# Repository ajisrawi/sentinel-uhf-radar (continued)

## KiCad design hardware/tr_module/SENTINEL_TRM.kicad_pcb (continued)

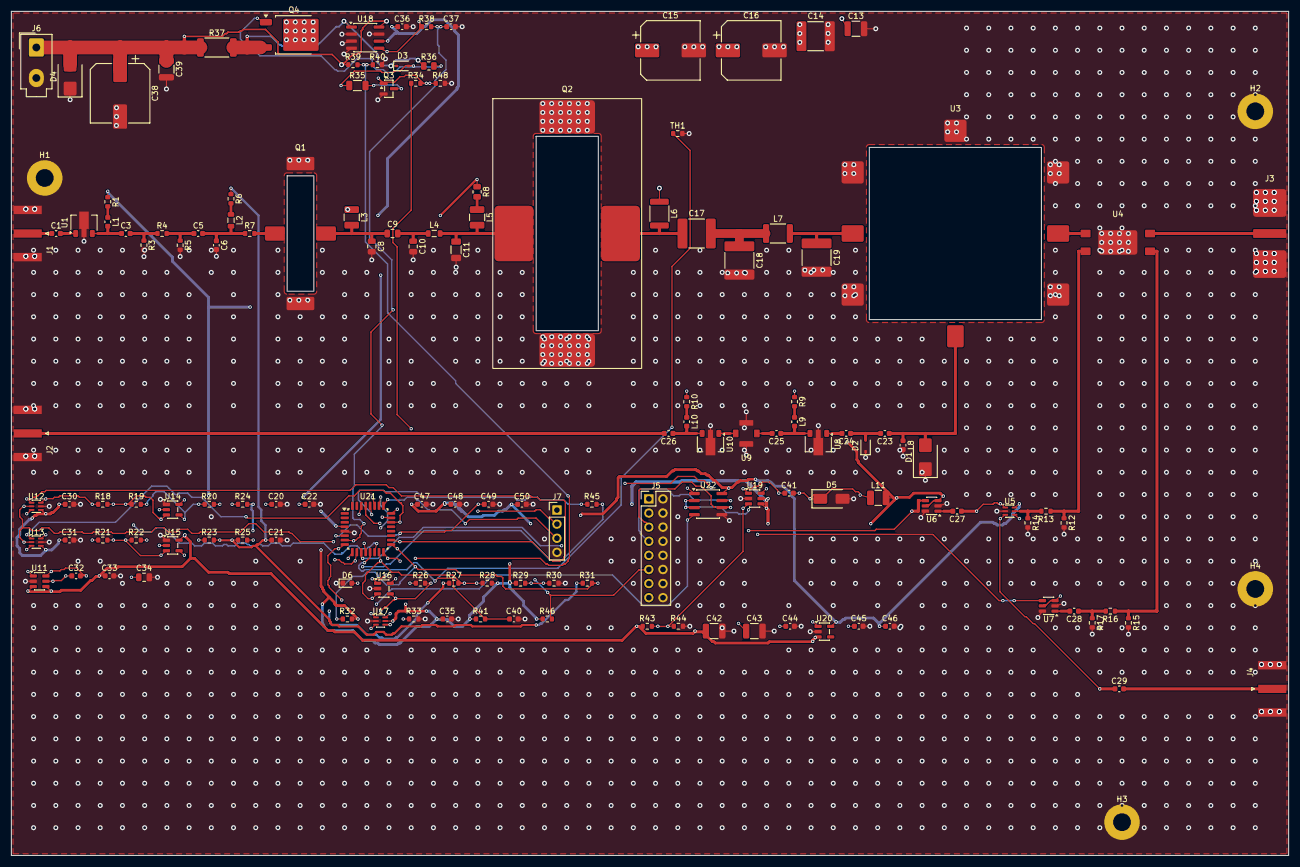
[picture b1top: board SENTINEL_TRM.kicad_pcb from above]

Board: 4 copper layers, 230.0 x 152.0 mm, 144 parts (0 on the bottom side), 90 nets.

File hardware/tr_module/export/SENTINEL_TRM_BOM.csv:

"Item","References","Qty","Value","Footprint","Description","MPN / part class"
"1","C1,C3,C23-C29","9","100p","Capacitor_SMD:C_0603_1608Metric","DC block, C0G",""
"2","C5","1","33p","Capacitor_SMD:C_0603_1608Metric","Driver input DC block",""
"3","C6","1","8.2p","Capacitor_SMD:C_0603_1608Metric","Driver input match",""
"4","C8","1","1.5p","Capacitor_SMD:C_0805_2012Metric","Driver output match",""
"5","C9","1","47p","Capacitor_SMD:C_0805_2012Metric","Interstage DC block",""
"6","C10","1","10p","Capacitor_SMD:C_0805_2012Metric","Interstage match",""
"7","C11","1","22p","Capacitor_SMD:C_1206_3216Metric","PA input match",""
"8","C13","1","1n 100V","Capacitor_SMD:C_1210_3225Metric","",""
"9","C14","1","10u 100V","Capacitor_SMD:C_2220_5750Metric","",""
"10","C15,C16","2","330u 63V","Capacitor_SMD:CP_Elec_10x10.5","Polymer, pulse reservoir",""
"11","C17","1","100p","Capacitor_SMD:C_2220_5750Metric","Output DC block, 500 V, high-Q",""
"12","C18","1","6.8p","Capacitor_SMD:C_2220_5750Metric","Output match, 500 V",""
"13","C19","1","3.3p","Capacitor_SMD:C_2220_5750Metric","Output match, 500 V",""
"14","C20,C21,C30,C31,C35,C36,C40,C41,C44,C47,C49,C50","12","100n","Capacitor_SMD:C_0603_1608Metric","",""
"15","C22,C32,C33,C45,C46","5","1u","Capacitor_SMD:C_0603_1608Metric","",""
"16","C34","1","4.7u","Capacitor_SMD:C_0805_2012Metric","",""
"17","C37","1","10n","Capacitor_SMD:C_0603_1608Metric","",""
"18","C38","1","100u 100V","Capacitor_SMD:CP_Elec_10x10.5","Bus bulk",""
"19","C39","1","1u 100V","Capacitor_SMD:C_1210_3225Metric","",""
"20","C42","1","22u","Capacitor_SMD:C_1210_3225Metric","",""
"21","C43","1","10u 50V","Capacitor_SMD:C_1210_3225Metric","",""
"22","C48","1","4.7u","Capacitor_SMD:C_0603_1608Metric","",""
"23","D1","1","PIN","Diode_SMD:D_SMB","Coarse PIN limiter diode, 100 W pk",""
"24","D2","1","Schottky","Diode_SMD:D_SOD-323","Fine limiter",""
"25","D3","1","12V","Diode_SMD:D_SOD-323","P-FET Vgs clamp",""
"26","D4","1","SMBJ58A","Diode_SMD:D_SMB","Bus transient clamp",""
"27","D5","1","SS16","Diode_SMD:D_SMA","",""
"28","D6","1","GRN","LED_SMD:LED_0603_1608Metric","Status LED",""
"29","H1-H4","4","M3","MountingHole:MountingHole_3.2mm_M3_Pad","Cold-plate bond, M3",""
"30","J1","1","TX_IN","Connector_Coaxial:SMA_Amphenol_132289_EdgeMount","SMA edge launch, RF drive from RFSoC DAC (0 dBm)",""
"31","J2","1","RX_OUT","Connector_Coaxial:SMA_Amphenol_132289_EdgeMount","SMA edge launch to RFSoC ADC",""
"32","J3","1","ANT","SENTINEL:N_EdgeLaunch","N-type edge launch to crossed-dipole hybrid",""
"33","J4","1","CAL","Connector_Coaxial:SMA_Amphenol_132289_EdgeMount","SMA to array calibration network (mutual-coupling cal)",""
"34","J5","1","BACKPLANE","Connector_PinHeader_2.54mm:PinHeader_2x08_P2.54mm_Vertical","Tile backplane: aux power, RS-485, TX_EN gate, fault; even pins ground",""
"35","J6","1","50V IN","Connector_Molex:Molex_Mini-Fit_Jr_5566-02A_2x01_P4.20mm_Vertical","Mini-Fit Jr, 50 V drain bus from subarray supply",""
"36","J7","1","SWD","Connector_PinHeader_2.54mm:PinHeader_1x04_P2.54mm_Vertical","",""
"37","L1,L9,L10","3","390n","Inductor_SMD:L_0603_1608Metric","RF choke",""
"38","L2","1","220n","Inductor_SMD:L_0805_2012Metric","Gate feed",""
"39","L3","1","120n","Inductor_SMD:L_1210_3225Metric","Driver drain feed",""
"40","L4","1","18n","Inductor_SMD:L_0805_2012Metric","Interstage match",""
"41","L5","1","56n","Inductor_SMD:L_1210_3225Metric","PA gate feed",""
"42","L6","1","47n","Inductor_SMD:L_1812_4532Metric","PA drain feed, 10 A peak",""
"43","L7","1","8n","Inductor_SMD:L_1812_4532Metric","Output match, air core",""
"44","L8","1","100n","Inductor_SMD:L_0603_1608Metric","Limiter DC return",""
"45","L11","1","22u","Inductor_SMD:L_1210_3225Metric","",""
"46","Q1","1","GaN 10W","SENTINEL:GaN_Flange_440166","Driver GaN HEMT 10 W, 50 V, 440166 flange","CG2H40010F class"
"47","Q2","1","GaN 300W","SENTINEL:GaN_Flange_780","Final GaN HEMT 300 W pulsed, 50 V, NI-780 flange","UHF radar GaN, 300 W class"
"48","Q3","1","2N7002","Package_TO_SOT_SMD:SOT-23","Level shifter",""
"49","Q4","1","SUD50P10","Package_TO_SOT_SMD:TO-252-2","High-side drain switch, 100 V P-FET",""
"50","R1,R10","2","33","Resistor_SMD:R_0603_1608Metric","",""
"51","R3,R5","2","292","Resistor_SMD:R_0603_1608Metric","3 dB pi pad",""
"52","R4","1","17.6","Resistor_SMD:R_0603_1608Metric","3 dB pi pad",""
"53","R6","1","22","Resistor_SMD:R_0603_1608Metric","",""
"54","R7","1","4.7","Resistor_SMD:R_0603_1608Metric","Gate stability resistor",""
"55","R8","1","10","Resistor_SMD:R_0805_2012Metric","",""
"56","R9","1","47","Resistor_SMD:R_0603_1608Metric","",""
"57","R12,R14,R15,R17","4","96","Resistor_SMD:R_0603_1608Metric","",""
"58","R13,R16","2","71","Resistor_SMD:R_0603_1608Metric","10 dB pi pad",""
"59","R18,R21,R26,R33,R40,R41,R44,R46","8","10k","Resistor_SMD:R_0603_1608Metric","TX_EN defaults low",""
"60","R19,R22","2","12.4k","Resistor_SMD:R_0603_1608Metric","",""
"61","R20,R23","2","10","Resistor_SMD:R_0603_1608Metric","",""
"62","R24,R25,R27,R28,R31,R32,R48","7","100k","Resistor_SMD:R_0603_1608Metric","Fail-safe pinch-off",""
"63","R29","1","82k","Resistor_SMD:R_0603_1608Metric","",""
"64","R30","1","20k","Resistor_SMD:R_0603_1608Metric","",""
"65","R34","1","100","Resistor_SMD:R_0603_1608Metric","",""
"66","R35","1","10k","Resistor_SMD:R_1206_3216Metric","",""
"67","R36","1","4.7k","Resistor_SMD:R_0805_2012Metric","",""
"68","R37","1","5m","Resistor_SMD:R_2512_6332Metric","Drain current shunt, Kelvin",""
"69","R38,R45","2","1k","Resistor_SMD:R_0603_1608Metric","",""
"70","R39","1","180k","Resistor_SMD:R_0603_1608Metric","",""
"71","R43","1","56.2k","Resistor_SMD:R_0603_1608Metric","",""
"72","TH1","1","10k NTC","Resistor_SMD:R_0603_1608Metric","On PA flange",""
"73","U1","1","GB 20dB","Package_TO_SOT_SMD:SOT-89-3","Driver gain block, G 20 dB, P1dB +21 dBm","PHA-13LN+ class"
"74","U3","1","CIRC 400W","SENTINEL:Circulator_DropIn_32mm","Drop-in circulator 420-450 MHz, 400 W pk, 20 dB isolation",""
"75","U4","1","-30dB","SENTINEL:DirCoupler_SMD_12x6","Directional coupler 30 dB, 500 W",""
"76","U5","1","SPDT","Package_TO_SOT_SMD:SOT-363_SC-70-6","RF switch: detector or calibration port",""
"77","U6","1","DET FWD","Package_TO_SOT_SMD:SOT-23-6","Forward power detector",""
"78","U7","1","DET REV","Package_TO_SOT_SMD:SOT-23-6","Reflected power detector (VSWR trip)",""
"79","U8","1","LNA","Package_TO_SOT_SMD:SOT-89-3","LNA NF 0.5 dB, G 18 dB at 435 MHz",""
"80","U9","1","BPF 420-450","SENTINEL:BPF_SMD_5x5","SAW BPF 435 MHz, 30 MHz BW, IL 2 dB",""
"81","U10","1","GB 20dB","Package_TO_SOT_SMD:SOT-89-3","Receive gain block, G 20 dB",""
"82","U11","1","LM2776","Package_TO_SOT_SMD:SOT-23-6","-5 V for GaN gate bias",""
"83","U12,U13","2","DAC7311","Package_TO_SOT_SMD:SOT-363_SC-70-6","12-bit DAC, DRV gate setpoint,12-bit DAC, PA gate setpoint",""
"84","U14,U15","2","LM321","Package_TO_SOT_SMD:SOT-23-5","Inverting gate driver, +5/-5 V",""
"85","U16","1","LMV331","Package_TO_SOT_SMD:SOT-23-5","BIAS_OK high only when VG_PA < -2.0 V",""
"86","U17","1","74LVC1G11","Package_TO_SOT_SMD:SOT-363_SC-70-6","Drain on = TX_EN AND BIAS_OK AND MCU enable",""
"87","U18","1","INA240A1","Package_SO:SOIC-8_3.9x4.9mm_P1.27mm","Drain current sense, 20 V/V",""
"88","U19","1","LMR16006","Package_TO_SOT_SMD:SOT-23-6","12 V to 5 V buck, 0.6 A",""
"89","U20","1","AP2112K-3.3","Package_TO_SOT_SMD:SOT-23-5","",""
"90","U21","1","STM32G031K8T6","Package_QFP:LQFP-32_7x7mm_P0.8mm","Module controller: bias, protection, telemetry",""
"91","U22","1","THVD1450","Package_SO:SOIC-8_3.9x4.9mm_P1.27mm","RS-485 to tile controller",""

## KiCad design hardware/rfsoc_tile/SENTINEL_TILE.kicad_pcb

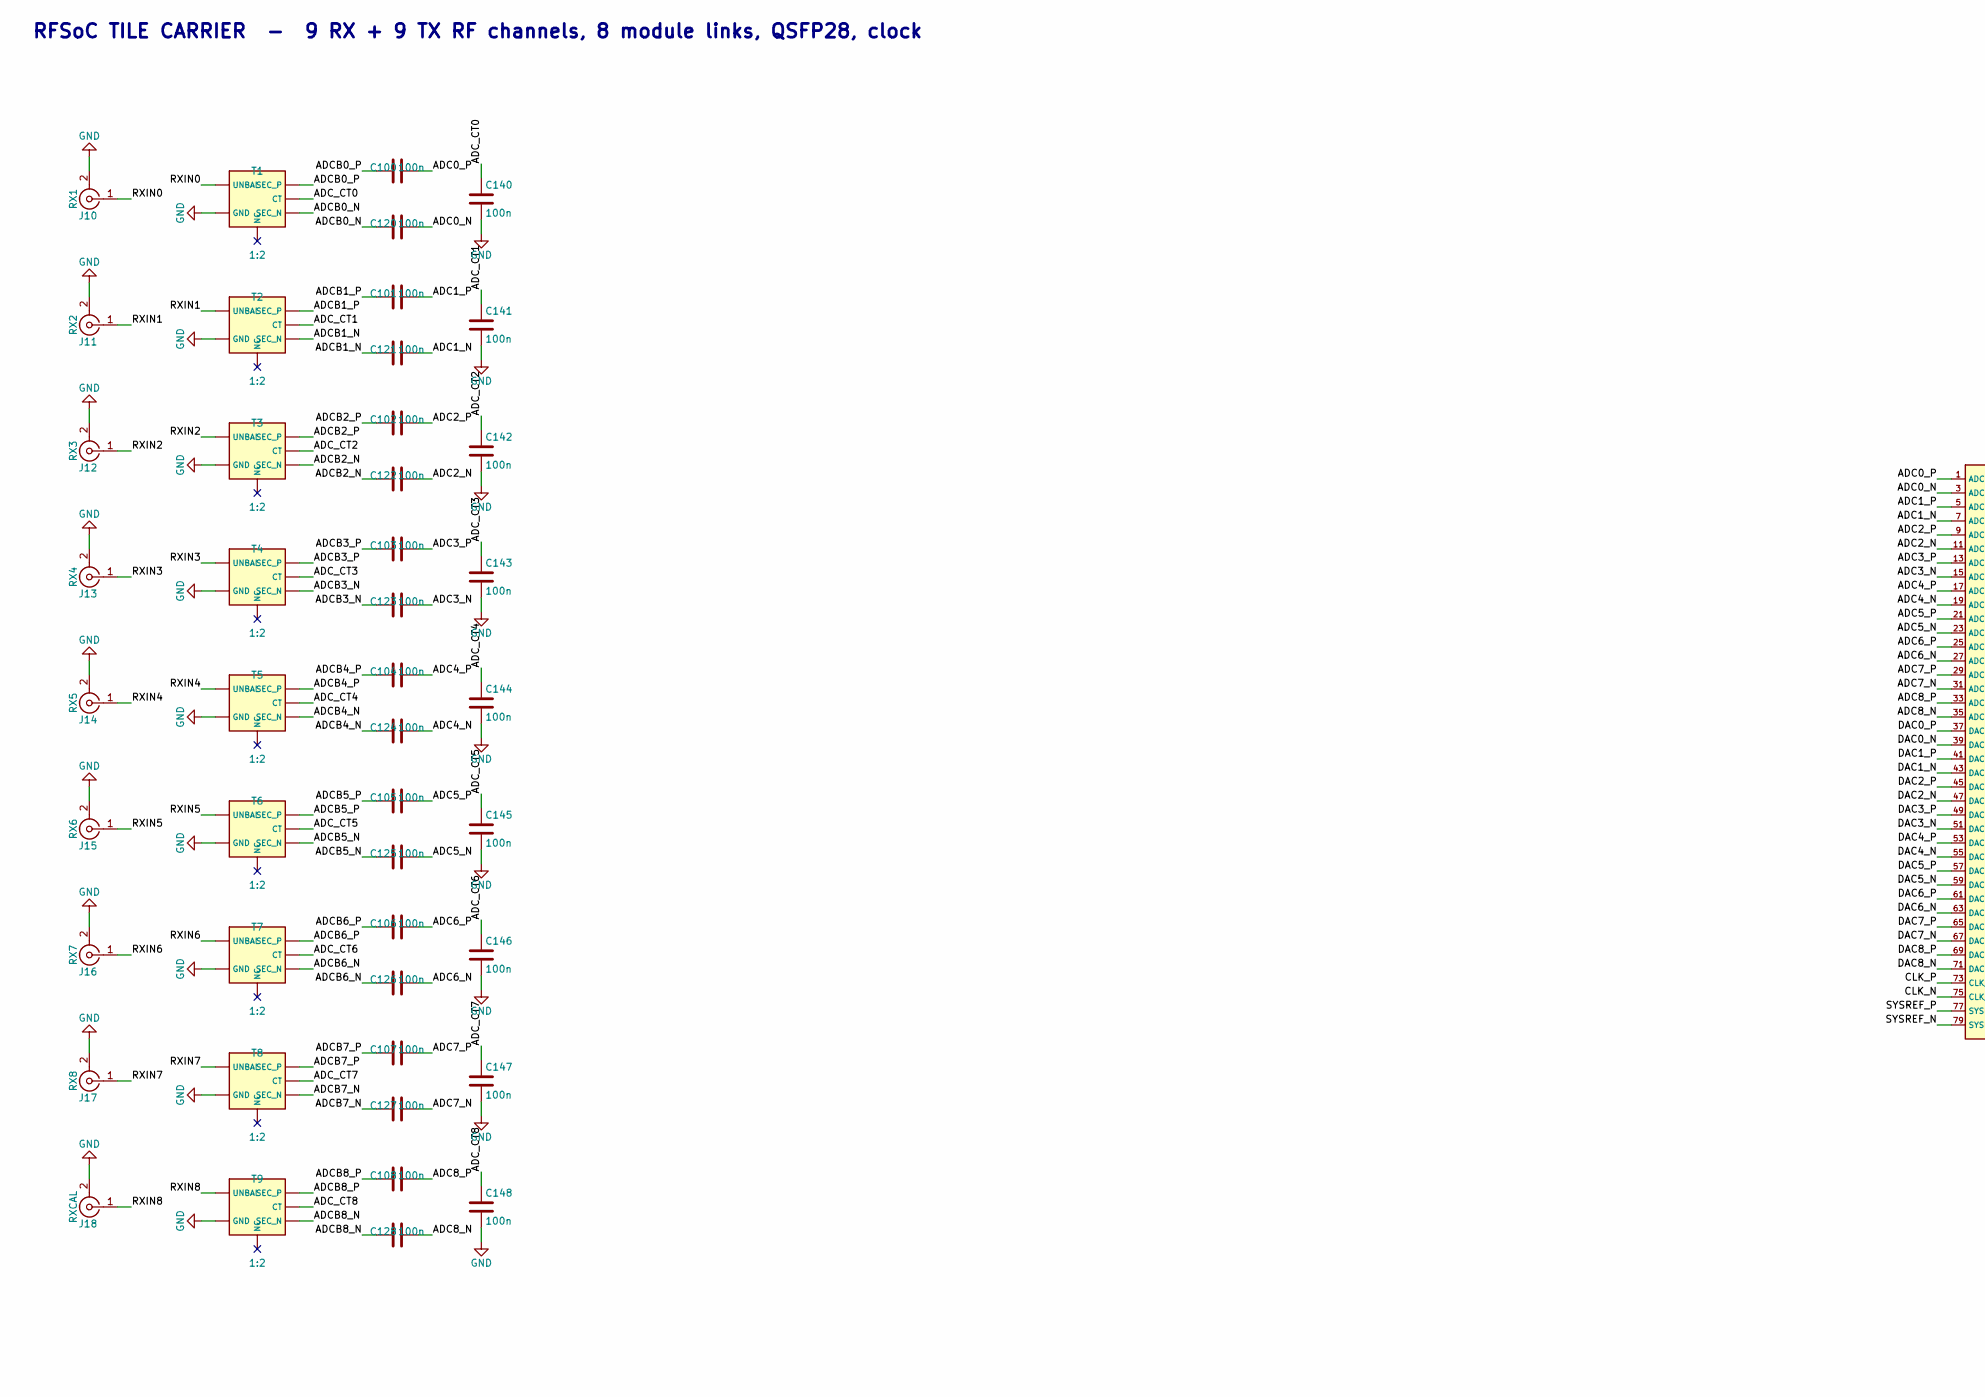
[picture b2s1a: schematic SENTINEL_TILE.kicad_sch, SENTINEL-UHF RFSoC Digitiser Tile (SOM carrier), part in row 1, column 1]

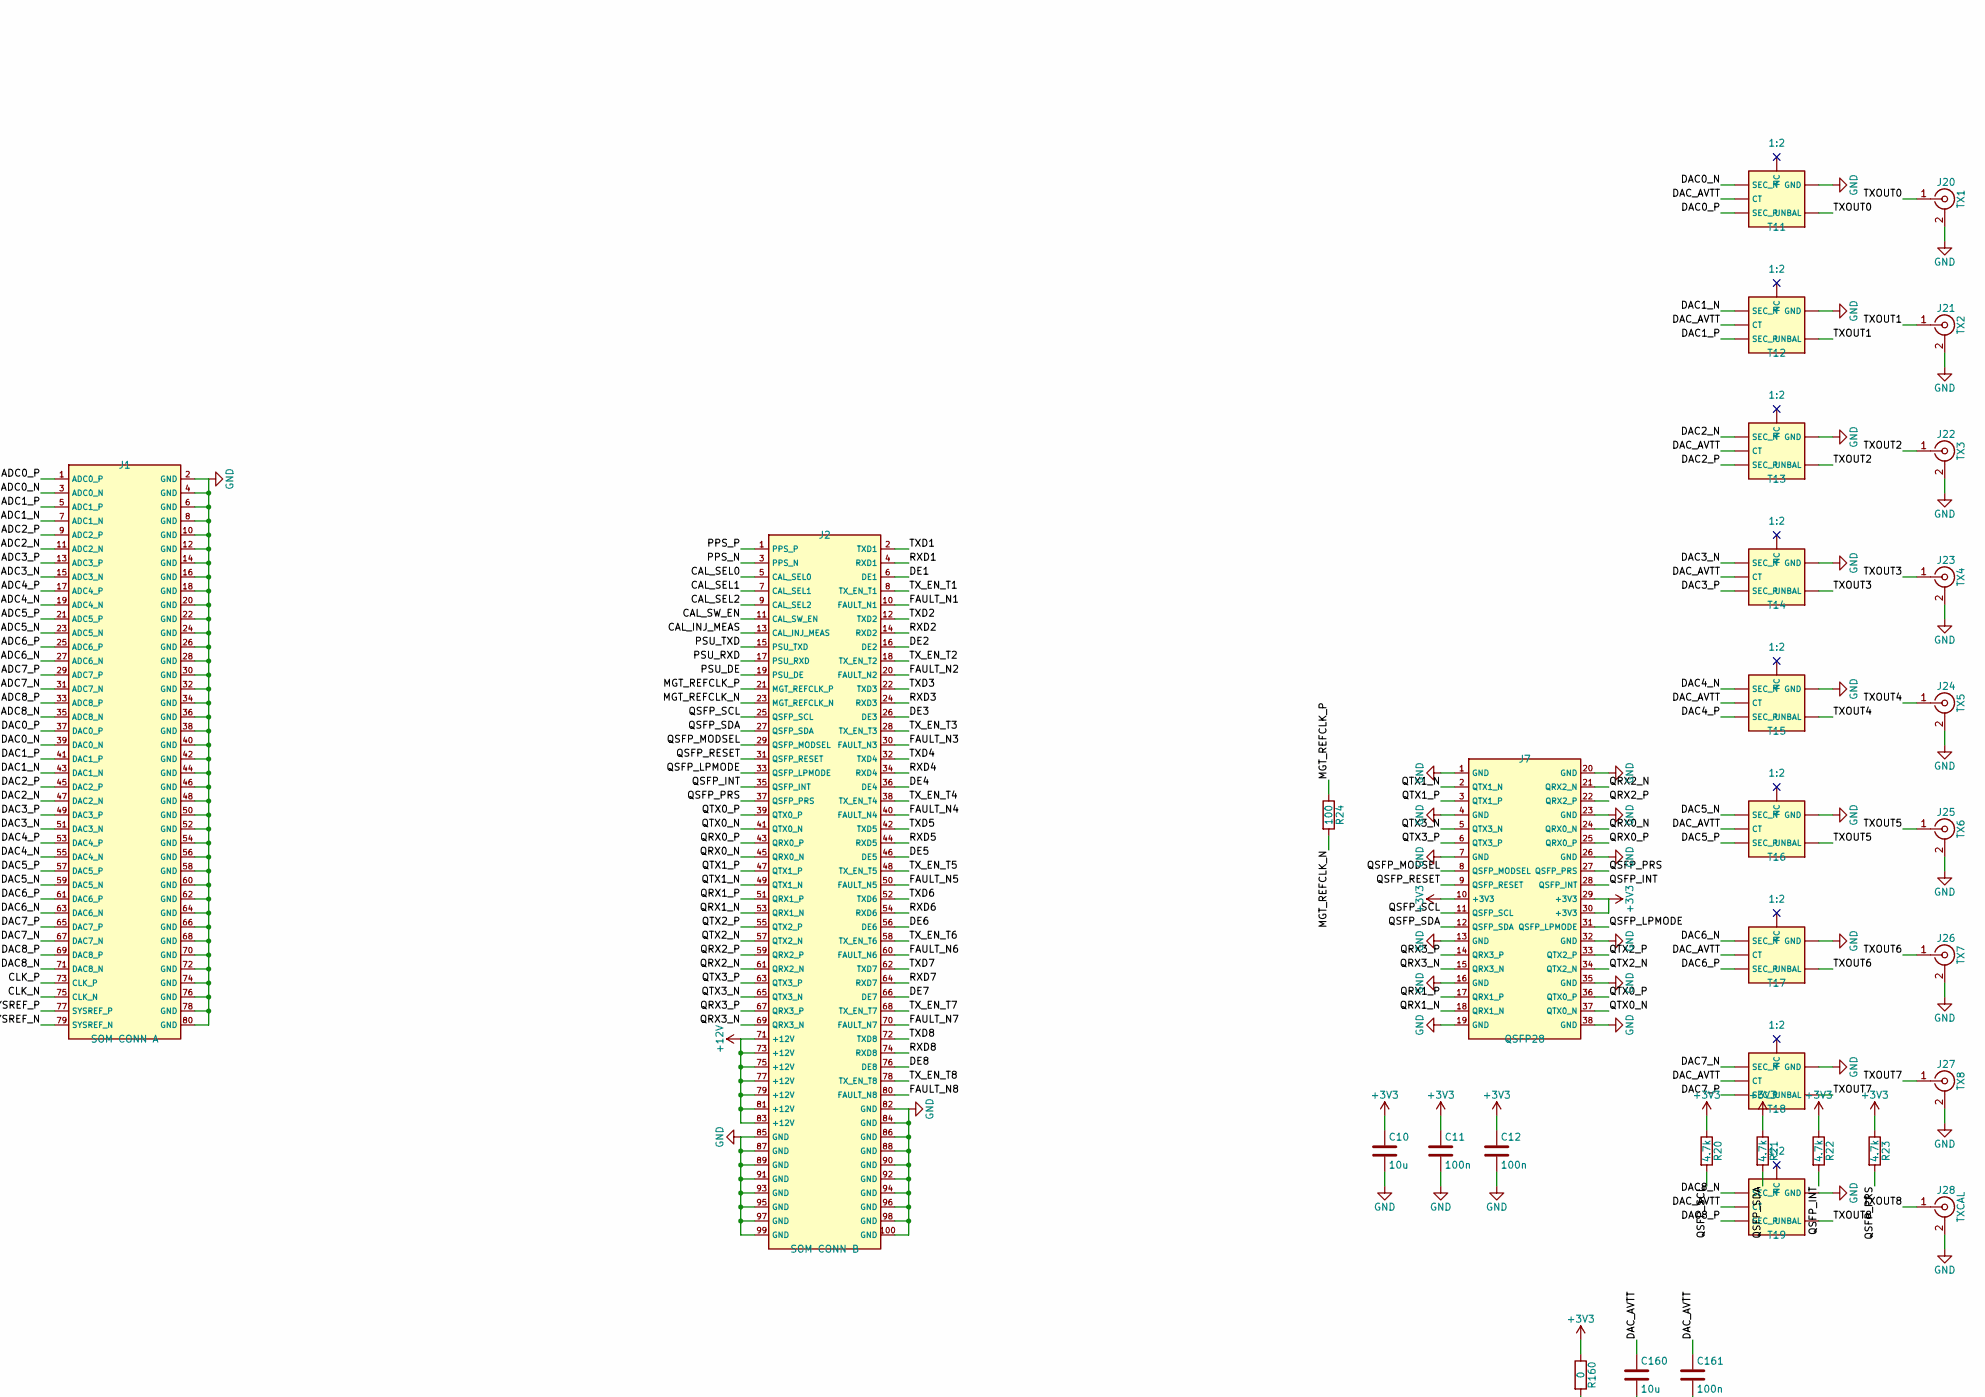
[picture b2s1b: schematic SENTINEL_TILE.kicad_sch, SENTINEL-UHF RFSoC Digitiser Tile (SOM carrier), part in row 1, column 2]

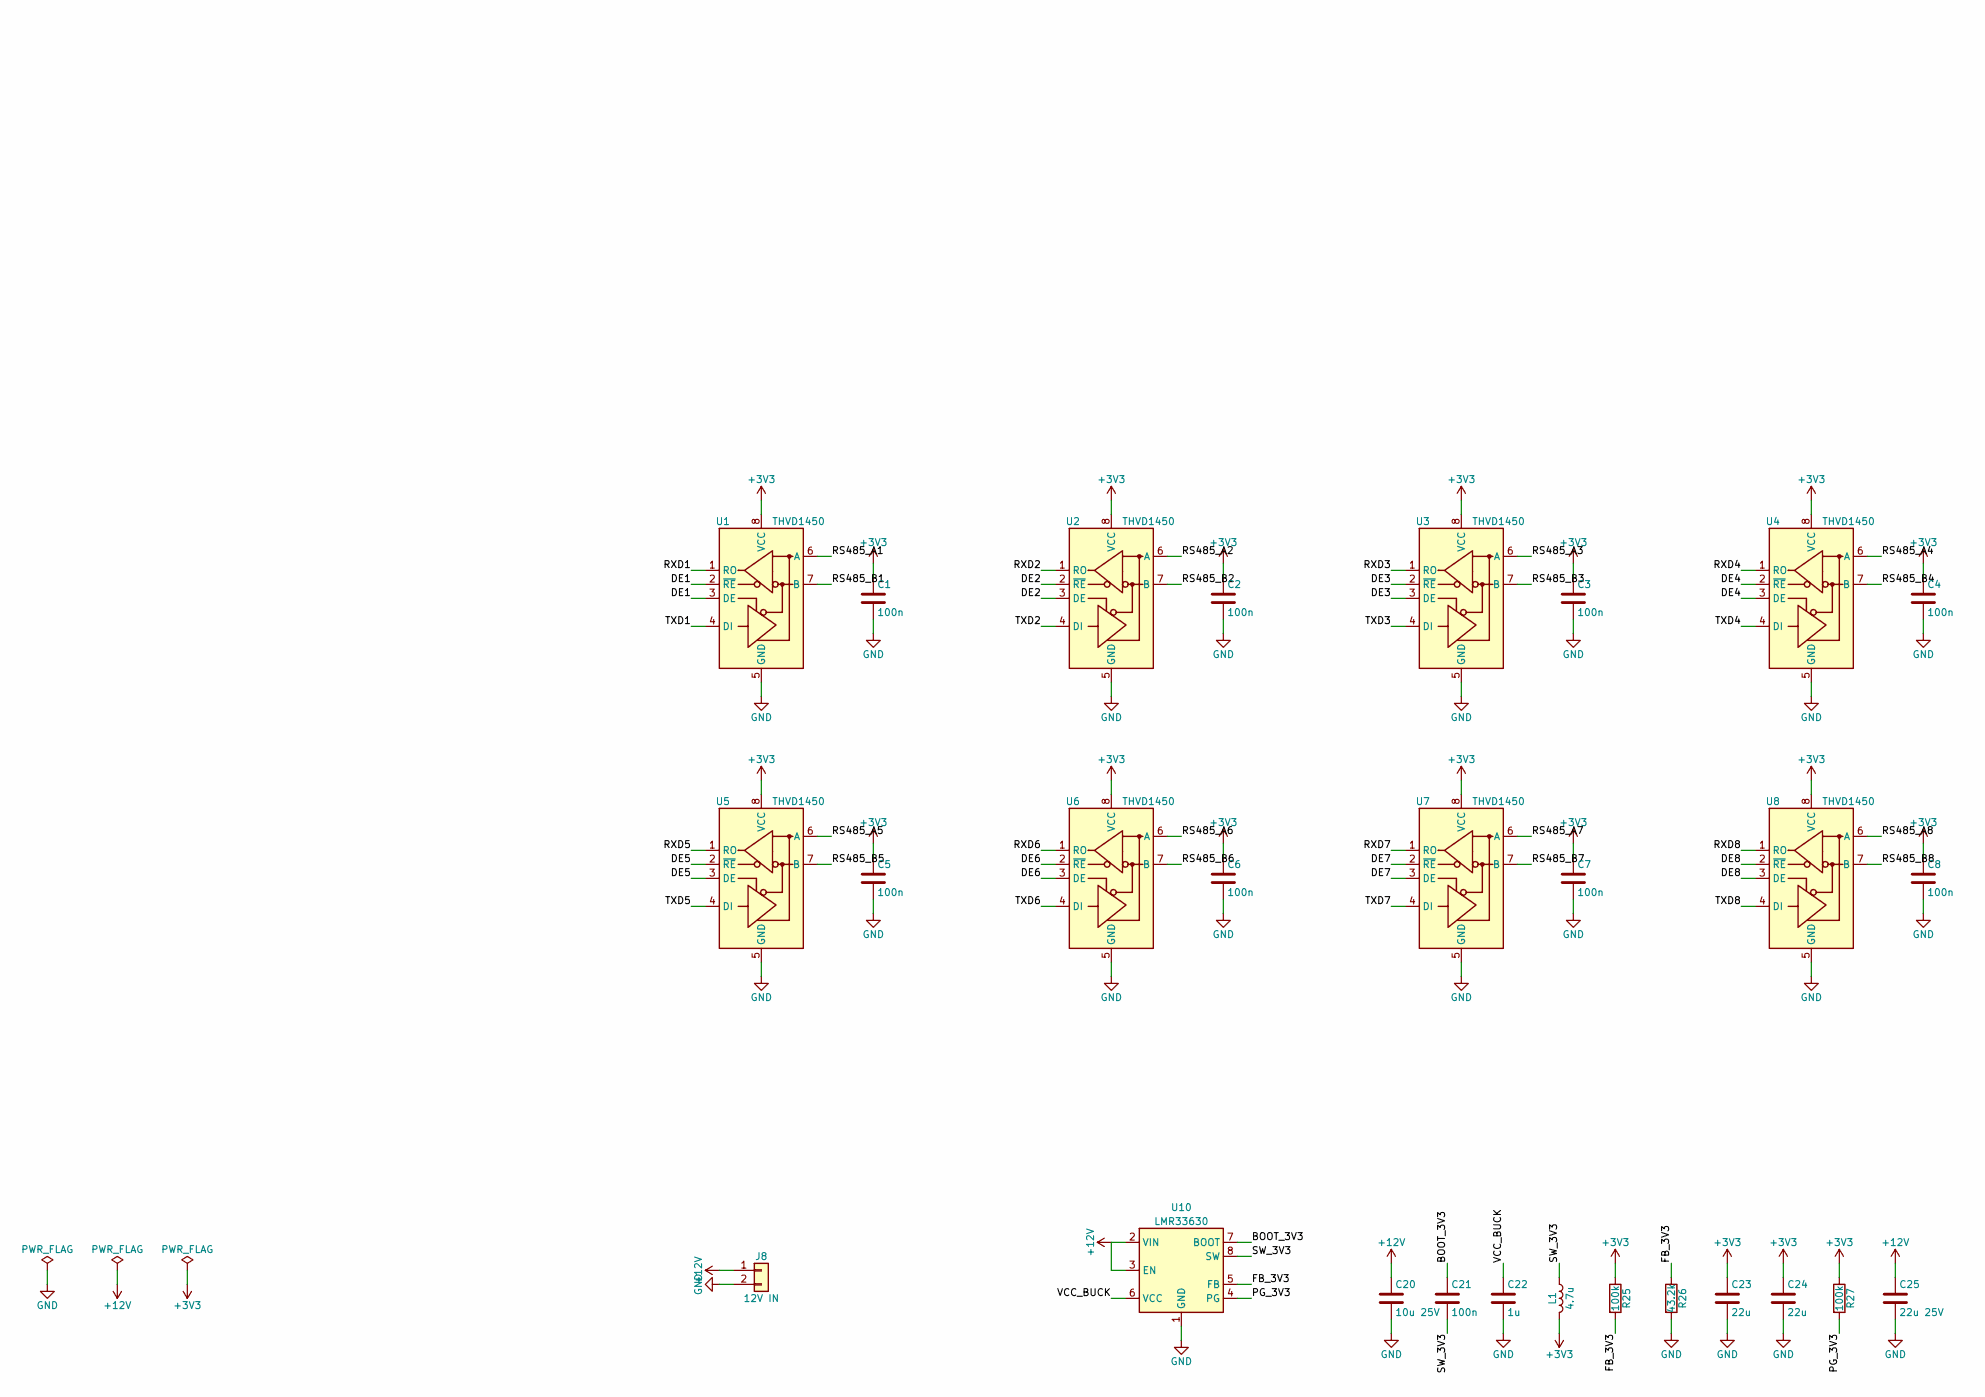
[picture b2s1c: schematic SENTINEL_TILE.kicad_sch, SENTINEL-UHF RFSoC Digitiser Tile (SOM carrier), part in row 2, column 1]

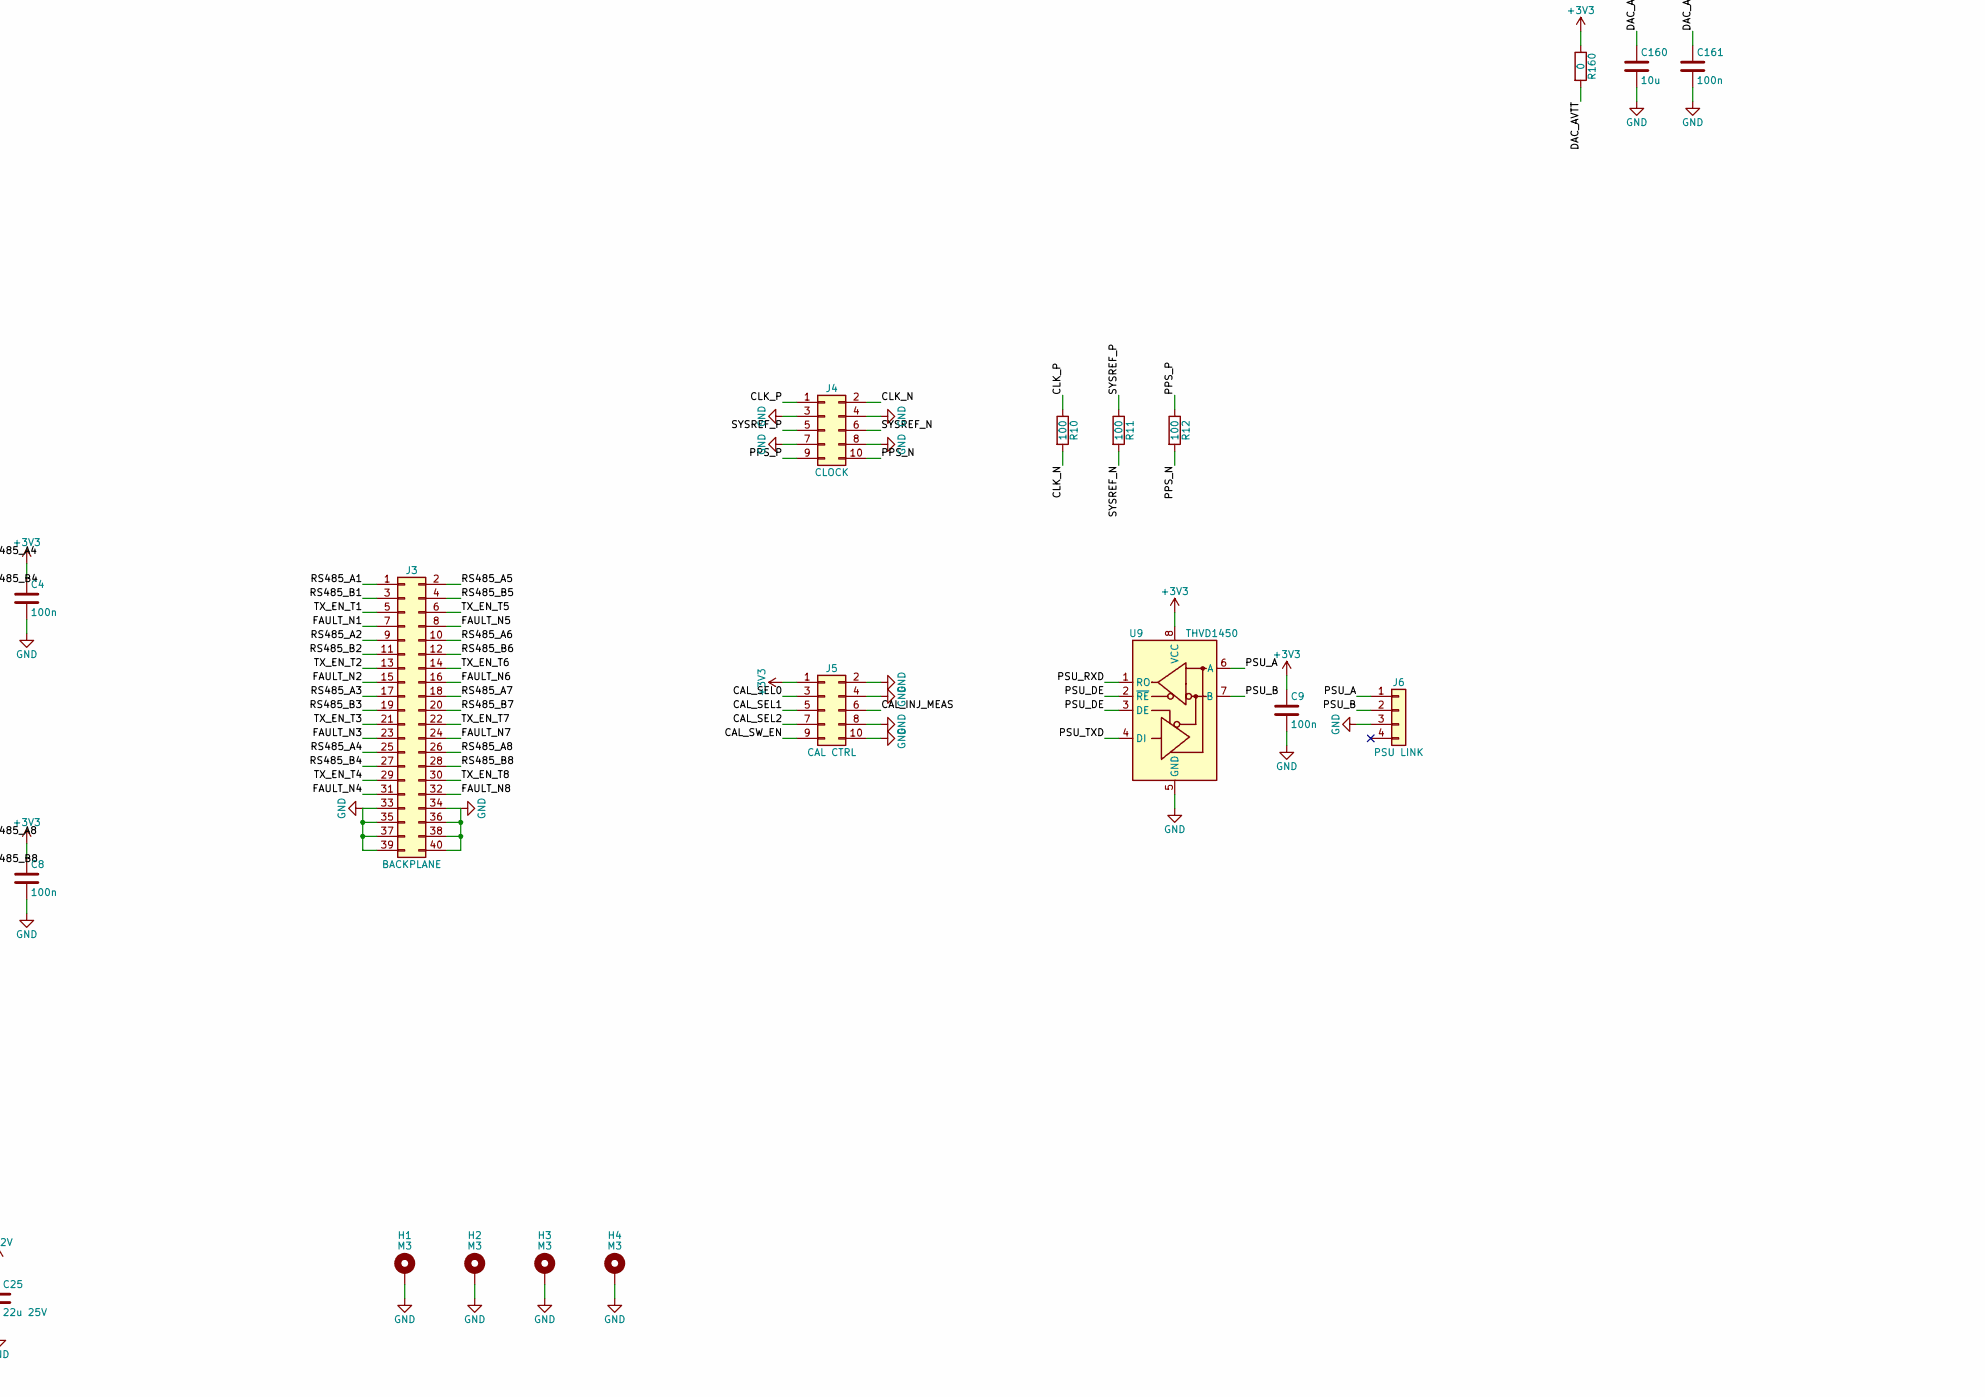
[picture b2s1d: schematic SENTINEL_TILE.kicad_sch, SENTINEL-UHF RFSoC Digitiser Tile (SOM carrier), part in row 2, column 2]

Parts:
C1, C2, C3, C4, C5, C6, C7, C8, C9, C11, C12, C21, C100, C101, C102, C103, C104, C105, C106, C107, C108, C120, C121, C122, C123, C124, C125, C126, C127, C128, C140, C141, C142, C143, C144, C145, C146, C147, C148, C161: 100n; C_0603_1608Metric
C10, C160: 10u; C_1210_3225Metric
C20: 10u 25V; C_1210_3225Metric
C22: 1u; C_0603_1608Metric
C23, C24: 22u; C_1210_3225Metric
C25: 22u 25V; C_1210_3225Metric
H1, H2, H3, H4: M3; MountingHole_3.2mm_M3_Pad
J1: SOM CONN A; SOM_B2B_2x40_P0.8
J2: SOM CONN B; SOM_B2B_2x50_P0.8
J3: BACKPLANE; PinHeader_2x20_P2.54mm_Vertical
J4: CLOCK; PinHeader_2x05_P2.54mm_Vertical
J5: CAL CTRL; PinHeader_2x05_P2.54mm_Vertical
J6: PSU LINK; PinHeader_1x04_P2.54mm_Vertical
J7: QSFP28; QSFP28_Host_38P
J8: 12V IN; Molex_Mini-Fit_Jr_5566-02A_2x01_P4.20mm_Vertical
J10: RX1; SMA_Amphenol_132289_EdgeMount
J11: RX2; SMA_Amphenol_132289_EdgeMount
J12: RX3; SMA_Amphenol_132289_EdgeMount
J13: RX4; SMA_Amphenol_132289_EdgeMount
J14: RX5; SMA_Amphenol_132289_EdgeMount
J15: RX6; SMA_Amphenol_132289_EdgeMount
J16: RX7; SMA_Amphenol_132289_EdgeMount
J17: RX8; SMA_Amphenol_132289_EdgeMount
J18: RXCAL; SMA_Amphenol_132289_EdgeMount
J20: TX1; SMA_Amphenol_132289_EdgeMount
J21: TX2; SMA_Amphenol_132289_EdgeMount
J22: TX3; SMA_Amphenol_132289_EdgeMount
J23: TX4; SMA_Amphenol_132289_EdgeMount
J24: TX5; SMA_Amphenol_132289_EdgeMount
J25: TX6; SMA_Amphenol_132289_EdgeMount
J26: TX7; SMA_Amphenol_132289_EdgeMount
J27: TX8; SMA_Amphenol_132289_EdgeMount
J28: TXCAL; SMA_Amphenol_132289_EdgeMount
L1: 4.7u; L_1210_3225Metric
R10, R11, R12, R24: 100; R_0603_1608Metric
R20, R21, R22, R23: 4.7k; R_0603_1608Metric
R25, R27: 100k; R_0603_1608Metric
R26: 43.2k; R_0603_1608Metric
R160: 0; R_0805_2012Metric
T1, T2, T3, T4, T5, T6, T7, T8, T9, T11, T12, T13, T14, T15, T16, T17, T18, T19: 1:2; Balun_SMD_6P_3.8x3.8
U1, U2, U3, U4, U5, U6, U7, U8, U9: THVD1450; SOIC-8_3.9x4.9mm_P1.27mm
U10: LMR33630; Texas_HSOP-8-1EP_3.9x4.9mm_P1.27mm_ThermalVias

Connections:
+3V3: C1.1, C2.1, C3.1, C4.1, C5.1, C6.1, C7.1, C8.1, C9.1, C10.1, C11.1, C12.1, C23.1, C24.1, J5.1, J7.10 (+3V3), J7.29 (+3V3), J7.30 (+3V3), L1.2, R20.1, R21.1, R22.1, R23.1, R25.1, R27.1, R160.1, U1.8 (VCC), U2.8 (VCC), U3.8 (VCC), U4.8 (VCC), U5.8 (VCC), U6.8 (VCC), U7.8 (VCC), U8.8 (VCC), U9.8 (VCC)
+12V: C20.1, C25.1, J2.71 (+12V), J2.73 (+12V), J2.75 (+12V), J2.77 (+12V), J2.79 (+12V), J2.81 (+12V), J2.83 (+12V), J8.1, U10.2 (VIN), U10.3 (EN)
ADC0_N: C120.2, J1.3 (ADC0_N)
ADC0_P: C100.2, J1.1 (ADC0_P)
ADC1_N: C121.2, J1.7 (ADC1_N)
ADC1_P: C101.2, J1.5 (ADC1_P)
ADC2_N: C122.2, J1.11 (ADC2_N)
ADC2_P: C102.2, J1.9 (ADC2_P)
ADC3_N: C123.2, J1.15 (ADC3_N)
ADC3_P: C103.2, J1.13 (ADC3_P)
ADC4_N: C124.2, J1.19 (ADC4_N)
ADC4_P: C104.2, J1.17 (ADC4_P)
ADC5_N: C125.2, J1.23 (ADC5_N)
ADC5_P: C105.2, J1.21 (ADC5_P)
ADC6_N: C126.2, J1.27 (ADC6_N)
ADC6_P: C106.2, J1.25 (ADC6_P)
ADC7_N: C127.2, J1.31 (ADC7_N)
ADC7_P: C107.2, J1.29 (ADC7_P)
ADC8_N: C128.2, J1.35 (ADC8_N)
ADC8_P: C108.2, J1.33 (ADC8_P)
ADCB0_N: C120.1, T1.4 (SEC_N)
ADCB0_P: C100.1, T1.3 (SEC_P)
ADCB1_N: C121.1, T2.4 (SEC_N)
ADCB1_P: C101.1, T2.3 (SEC_P)
ADCB2_N: C122.1, T3.4 (SEC_N)
ADCB2_P: C102.1, T3.3 (SEC_P)
ADCB3_N: C123.1, T4.4 (SEC_N)
ADCB3_P: C103.1, T4.3 (SEC_P)
ADCB4_N: C124.1, T5.4 (SEC_N)
ADCB4_P: C104.1, T5.3 (SEC_P)
ADCB5_N: C125.1, T6.4 (SEC_N)
ADCB5_P: C105.1, T6.3 (SEC_P)
ADCB6_N: C126.1, T7.4 (SEC_N)
ADCB6_P: C106.1, T7.3 (SEC_P)
ADCB7_N: C127.1, T8.4 (SEC_N)
ADCB7_P: C107.1, T8.3 (SEC_P)
ADCB8_N: C128.1, T9.4 (SEC_N)
ADCB8_P: C108.1, T9.3 (SEC_P)
ADC_CT0: C140.1, T1.5 (CT)
ADC_CT1: C141.1, T2.5 (CT)
ADC_CT2: C142.1, T3.5 (CT)
ADC_CT3: C143.1, T4.5 (CT)
ADC_CT4: C144.1, T5.5 (CT)
ADC_CT5: C145.1, T6.5 (CT)
ADC_CT6: C146.1, T7.5 (CT)
ADC_CT7: C147.1, T8.5 (CT)
ADC_CT8: C148.1, T9.5 (CT)
BOOT_3V3: C21.1, U10.7 (BOOT)
CAL_INJ_MEAS: J2.13 (CAL_INJ_MEAS), J5.6
CAL_SEL0: J2.5 (CAL_SEL0), J5.3
CAL_SEL1: J2.7 (CAL_SEL1), J5.5
CAL_SEL2: J2.9 (CAL_SEL2), J5.7
CAL_SW_EN: J2.11 (CAL_SW_EN), J5.9
CLK_N: J1.75 (CLK_N), J4.2, R10.2
CLK_P: J1.73 (CLK_P), J4.1, R10.1
DAC0_N: J1.39 (DAC0_N), T11.4 (SEC_N)
DAC0_P: J1.37 (DAC0_P), T11.3 (SEC_P)
DAC1_N: J1.43 (DAC1_N), T12.4 (SEC_N)
DAC1_P: J1.41 (DAC1_P), T12.3 (SEC_P)
DAC2_N: J1.47 (DAC2_N), T13.4 (SEC_N)
DAC2_P: J1.45 (DAC2_P), T13.3 (SEC_P)
DAC3_N: J1.51 (DAC3_N), T14.4 (SEC_N)
DAC3_P: J1.49 (DAC3_P), T14.3 (SEC_P)
DAC4_N: J1.55 (DAC4_N), T15.4 (SEC_N)
DAC4_P: J1.53 (DAC4_P), T15.3 (SEC_P)
DAC5_N: J1.59 (DAC5_N), T16.4 (SEC_N)
DAC5_P: J1.57 (DAC5_P), T16.3 (SEC_P)
DAC6_N: J1.63 (DAC6_N), T17.4 (SEC_N)
DAC6_P: J1.61 (DAC6_P), T17.3 (SEC_P)
DAC7_N: J1.67 (DAC7_N), T18.4 (SEC_N)
DAC7_P: J1.65 (DAC7_P), T18.3 (SEC_P)
DAC8_N: J1.71 (DAC8_N), T19.4 (SEC_N)
DAC8_P: J1.69 (DAC8_P), T19.3 (SEC_P)
DAC_AVTT: C160.1, C161.1, R160.2, T11.5 (CT), T12.5 (CT), T13.5 (CT), T14.5 (CT), T15.5 (CT), T16.5 (CT), T17.5 (CT), T18.5 (CT), T19.5 (CT)
DE1: J2.6 (DE1), U1.2 (~RE), U1.3 (DE)
DE2: J2.16 (DE2), U2.2 (~RE), U2.3 (DE)
DE3: J2.26 (DE3), U3.2 (~RE), U3.3 (DE)
DE4: J2.36 (DE4), U4.2 (~RE), U4.3 (DE)
DE5: J2.46 (DE5), U5.2 (~RE), U5.3 (DE)
DE6: J2.56 (DE6), U6.2 (~RE), U6.3 (DE)
DE7: J2.66 (DE7), U7.2 (~RE), U7.3 (DE)
DE8: J2.76 (DE8), U8.2 (~RE), U8.3 (DE)
FAULT_N1: J2.10 (FAULT_N1), J3.7
FAULT_N2: J2.20 (FAULT_N2), J3.15
FAULT_N3: J2.30 (FAULT_N3), J3.23
FAULT_N4: J2.40 (FAULT_N4), J3.31
FAULT_N5: J2.50 (FAULT_N5), J3.8
FAULT_N6: J2.60 (FAULT_N6), J3.16
FAULT_N7: J2.70 (FAULT_N7), J3.24
FAULT_N8: J2.80 (FAULT_N8), J3.32
FB_3V3: R25.2, R26.1, U10.5 (FB)
GND: C1.2, C2.2, C3.2, C4.2, C5.2, C6.2, C7.2, C8.2, C9.2, C10.2, C11.2, C12.2, C20.2, C22.2, C23.2, C24.2, C25.2, C140.2, C141.2, C142.2, C143.2, C144.2, C145.2, C146.2, C147.2, C148.2, C160.2, C161.2, H1.1, H2.1, H3.1, H4.1, J1.2 (GND), J1.4 (GND), J1.6 (GND), J1.8 (GND), J1.10 (GND), J1.12 (GND), J1.14 (GND), J1.16 (GND), J1.18 (GND), J1.20 (GND), J1.22 (GND), J1.24 (GND), J1.26 (GND), J1.28 (GND), J1.30 (GND), J1.32 (GND), J1.34 (GND), J1.36 (GND), J1.38 (GND), J1.40 (GND), J1.42 (GND), J1.44 (GND), J1.46 (GND), J1.48 (GND), J1.50 (GND), J1.52 (GND), J1.54 (GND), J1.56 (GND), J1.58 (GND), J1.60 (GND), J1.62 (GND), J1.64 (GND), J1.66 (GND), J1.68 (GND), J1.70 (GND), J1.72 (GND), J1.74 (GND), J1.76 (GND), J1.78 (GND), J1.80 (GND), J2.82 (GND), J2.84 (GND), J2.85 (GND), J2.86 (GND), J2.87 (GND), J2.88 (GND), J2.89 (GND), J2.90 (GND), J2.91 (GND), J2.92 (GND), J2.93 (GND), J2.94 (GND), J2.95 (GND), J2.96 (GND), J2.97 (GND), J2.98 (GND), J2.99 (GND), J2.100 (GND), J3.33, J3.34, J3.35, J3.36, J3.37, J3.38, J3.39, J3.40, J4.3, J4.4, J4.7, J4.8, J5.2, J5.4, J5.8, J5.10, J6.3, J7.1 (GND), J7.4 (GND), J7.7 (GND), J7.13 (GND), J7.16 (GND), J7.19 (GND), J7.20 (GND), J7.23 (GND), J7.26 (GND), J7.32 (GND), J7.35 (GND), J7.38 (GND), J8.2, J10.2 (Ext), J11.2 (Ext), J12.2 (Ext), J13.2 (Ext), J14.2 (Ext), J15.2 (Ext), J16.2 (Ext), J17.2 (Ext), J18.2 (Ext), J20.2 (Ext), J21.2 (Ext), J22.2 (Ext), J23.2 (Ext), J24.2 (Ext), J25.2 (Ext), J26.2 (Ext), J27.2 (Ext), J28.2 (Ext), R26.2, T1.2 (GND), T2.2 (GND), T3.2 (GND), T4.2 (GND), T5.2 (GND), T6.2 (GND), T7.2 (GND), T8.2 (GND), T9.2 (GND), T11.2 (GND), T12.2 (GND), T13.2 (GND), T14.2 (GND), T15.2 (GND), T16.2 (GND), T17.2 (GND), T18.2 (GND), T19.2 (GND), U1.5 (GND), U2.5 (GND), U3.5 (GND), U4.5 (GND), U5.5 (GND), U6.5 (GND), U7.5 (GND), U8.5 (GND), U9.5 (GND), U10.1 (GND), U10.9 (GND)
MGT_REFCLK_N: J2.23 (MGT_REFCLK_N), R24.2
MGT_REFCLK_P: J2.21 (MGT_REFCLK_P), R24.1
PG_3V3: R27.2, U10.4 (PG)
PPS_N: J2.3 (PPS_N), J4.10, R12.2
PPS_P: J2.1 (PPS_P), J4.9, R12.1
PSU_A: J6.1, U9.6 (A)
PSU_B: J6.2, U9.7 (B)
PSU_DE: J2.19 (PSU_DE), U9.2 (~RE), U9.3 (DE)
PSU_RXD: J2.17 (PSU_RXD), U9.1 (RO)
PSU_TXD: J2.15 (PSU_TXD), U9.4 (DI)
QRX0_N: J2.45 (QRX0_N), J7.24 (QRX0_N)
QRX0_P: J2.43 (QRX0_P), J7.25 (QRX0_P)
QRX1_N: J2.53 (QRX1_N), J7.18 (QRX1_N)
QRX1_P: J2.51 (QRX1_P), J7.17 (QRX1_P)
QRX2_N: J2.61 (QRX2_N), J7.21 (QRX2_N)
QRX2_P: J2.59 (QRX2_P), J7.22 (QRX2_P)
QRX3_N: J2.69 (QRX3_N), J7.15 (QRX3_N)
QRX3_P: J2.67 (QRX3_P), J7.14 (QRX3_P)
QSFP_INT: J2.35 (QSFP_INT), J7.28 (QSFP_INT), R22.2
QSFP_LPMODE: J2.33 (QSFP_LPMODE), J7.31 (QSFP_LPMODE)
QSFP_MODSEL: J2.29 (QSFP_MODSEL), J7.8 (QSFP_MODSEL)
QSFP_PRS: J2.37 (QSFP_PRS), J7.27 (QSFP_PRS), R23.2
QSFP_RESET: J2.31 (QSFP_RESET), J7.9 (QSFP_RESET)
QSFP_SCL: J2.25 (QSFP_SCL), J7.11 (QSFP_SCL), R20.2
QSFP_SDA: J2.27 (QSFP_SDA), J7.12 (QSFP_SDA), R21.2
QTX0_N: J2.41 (QTX0_N), J7.37 (QTX0_N)
QTX0_P: J2.39 (QTX0_P), J7.36 (QTX0_P)
QTX1_N: J2.49 (QTX1_N), J7.2 (QTX1_N)
QTX1_P: J2.47 (QTX1_P), J7.3 (QTX1_P)
QTX2_N: J2.57 (QTX2_N), J7.34 (QTX2_N)
QTX2_P: J2.55 (QTX2_P), J7.33 (QTX2_P)
QTX3_N: J2.65 (QTX3_N), J7.5 (QTX3_N)
QTX3_P: J2.63 (QTX3_P), J7.6 (QTX3_P)
RS485_A1: J3.1, U1.6 (A)
RS485_A2: J3.9, U2.6 (A)
RS485_A3: J3.17, U3.6 (A)
RS485_A4: J3.25, U4.6 (A)
RS485_A5: J3.2, U5.6 (A)
RS485_A6: J3.10, U6.6 (A)
RS485_A7: J3.18, U7.6 (A)
RS485_A8: J3.26, U8.6 (A)
RS485_B1: J3.3, U1.7 (B)
RS485_B2: J3.11, U2.7 (B)
RS485_B3: J3.19, U3.7 (B)
RS485_B4: J3.27, U4.7 (B)
RS485_B5: J3.4, U5.7 (B)
RS485_B6: J3.12, U6.7 (B)
RS485_B7: J3.20, U7.7 (B)
RS485_B8: J3.28, U8.7 (B)
RXD1: J2.4 (RXD1), U1.1 (RO)
RXD2: J2.14 (RXD2), U2.1 (RO)
RXD3: J2.24 (RXD3), U3.1 (RO)
RXD4: J2.34 (RXD4), U4.1 (RO)
RXD5: J2.44 (RXD5), U5.1 (RO)
RXD6: J2.54 (RXD6), U6.1 (RO)
RXD7: J2.64 (RXD7), U7.1 (RO)
RXD8: J2.74 (RXD8), U8.1 (RO)
RXIN0: J10.1 (In), T1.1 (UNBAL)
RXIN1: J11.1 (In), T2.1 (UNBAL)
RXIN2: J12.1 (In), T3.1 (UNBAL)
RXIN3: J13.1 (In), T4.1 (UNBAL)
RXIN4: J14.1 (In), T5.1 (UNBAL)
RXIN5: J15.1 (In), T6.1 (UNBAL)
RXIN6: J16.1 (In), T7.1 (UNBAL)
RXIN7: J17.1 (In), T8.1 (UNBAL)
RXIN8: J18.1 (In), T9.1 (UNBAL)
SW_3V3: C21.2, L1.1, U10.8 (SW)
SYSREF_N: J1.79 (SYSREF_N), J4.6, R11.2
SYSREF_P: J1.77 (SYSREF_P), J4.5, R11.1
TXD1: J2.2 (TXD1), U1.4 (DI)
TXD2: J2.12 (TXD2), U2.4 (DI)
TXD3: J2.22 (TXD3), U3.4 (DI)
TXD4: J2.32 (TXD4), U4.4 (DI)
TXD5: J2.42 (TXD5), U5.4 (DI)
TXD6: J2.52 (TXD6), U6.4 (DI)
TXD7: J2.62 (TXD7), U7.4 (DI)
TXD8: J2.72 (TXD8), U8.4 (DI)
TXOUT0: J20.1 (In), T11.1 (UNBAL)
TXOUT1: J21.1 (In), T12.1 (UNBAL)
TXOUT2: J22.1 (In), T13.1 (UNBAL)
TXOUT3: J23.1 (In), T14.1 (UNBAL)
TXOUT4: J24.1 (In), T15.1 (UNBAL)
TXOUT5: J25.1 (In), T16.1 (UNBAL)
TXOUT6: J26.1 (In), T17.1 (UNBAL)
TXOUT7: J27.1 (In), T18.1 (UNBAL)
TXOUT8: J28.1 (In), T19.1 (UNBAL)
TX_EN_T1: J2.8 (TX_EN_T1), J3.5
TX_EN_T2: J2.18 (TX_EN_T2), J3.13
TX_EN_T3: J2.28 (TX_EN_T3), J3.21
TX_EN_T4: J2.38 (TX_EN_T4), J3.29
TX_EN_T5: J2.48 (TX_EN_T5), J3.6
TX_EN_T6: J2.58 (TX_EN_T6), J3.14
TX_EN_T7: J2.68 (TX_EN_T7), J3.22
TX_EN_T8: J2.78 (TX_EN_T8), J3.30
VCC_BUCK: C22.1, U10.6 (VCC)

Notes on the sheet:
RFSoC TILE CARRIER - 9 RX + 9 TX RF channels, 8 module links, QSFP28, clock
